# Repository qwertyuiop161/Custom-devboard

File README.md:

##Description

This is a custom devboard made with an ESP32-S3-WROOM-1 module using the preinstalled firmware. It uses a usb controller and a usb C port, with 5 main capacitors and 6 main resistors, along with 3 leds. the back (because im not good enough to have it all one sided YET (still learning (wow double paren (WOW QUAD PAREN)))) hsa an addressable LES with 2 more resistors and another capacitors.
I choose the ESP chip because of its power compared to arduino, WIFI and bluetooth capability, ease of wiring, and use of use. It has 40 pins, with 30 usable GPIO i think; also just wanted to mention that semicolon was a typo its just kinda funna that im so used to java and C that i accidentally end every sentence in typing with semicolon (even accidentally did iton this before correcting).

##Images:

###Schematic image:

Image of schematic:
<br>

###PCB images:

PCB full
<br>

PCB pads and zones
<br>

PCB tracks and vias
<br>

###3D Model images:

3D model front
<br>

3D model back
<br>

###BOM image:

BOM
<br>

###Bult Board:

Built Board! (sorry for low quality I have a bad camera):

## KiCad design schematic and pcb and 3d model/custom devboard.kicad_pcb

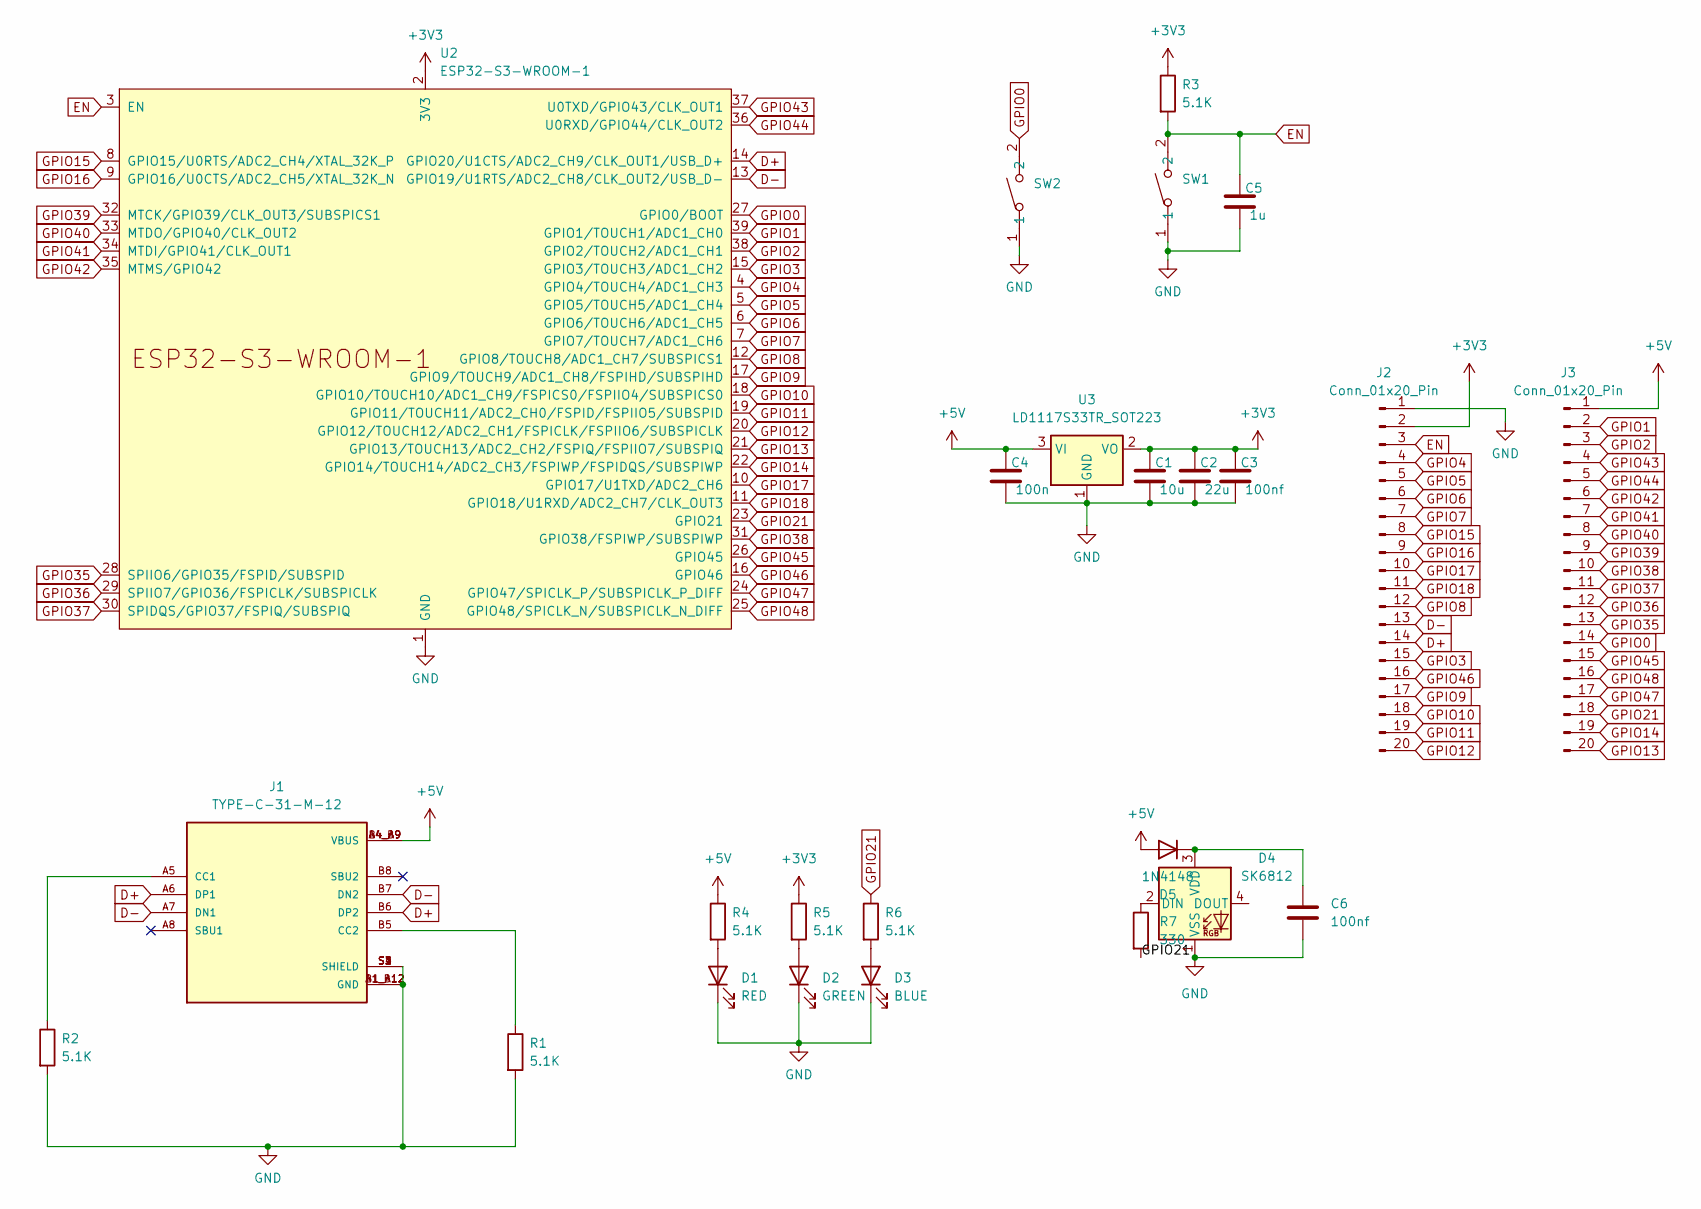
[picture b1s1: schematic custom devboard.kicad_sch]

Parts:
C1: 10u; C_0603_1608Metric
C2: 22u; C_0603_1608Metric
C3, C6: 100nf; C_0603_1608Metric
C4: 100n; C_0603_1608Metric
C5: 1u; C_0603_1608Metric
D1: RED; LED_0603_1608Metric
D2: GREEN; LED_0603_1608Metric
D3: BLUE; LED_0603_1608Metric
D4: SK6812; LED_SK6812_PLCC4_5.0x5.0mm_P3.2mm
D5: 1N4148; D_0603_1608Metric
J1: TYPE-C-31-M-12; HRO_TYPE-C-31-M-12; PARTREV 2020.12.08
J2, J3: Conn_01x20_Pin; PinHeader_1x20_P2.54mm_Vertical
R1, R2, R3, R4, R5, R6: 5.1K; R_0603_1608Metric
R7: 330; R_0603_1608Metric
SW1, SW2: TS-1088-AR02016; SW-SMD_L3.9-W3.0-P4.45; LCSC Part C720477
U2: ESP32-S3-WROOM-1
U3: LD1117S33TR_SOT223; SOT-223-3_TabPin2

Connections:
+3V3: C1.1, C2.1, C3.1, J2.2, R3.1, R5.1, U2.2 (3V3), U3.2 (VO)
+5V: C4.1, D5.2 (A), J1.A4_B9 (VBUS), J1.B4_A9 (VBUS), J3.1, R4.1, U3.3 (VI)
D+: J1.A6 (DP1), J1.B6 (DP2), J2.14, U2.14 (GPIO20/U1CTS/ADC2_CH9/CLK_OUT1/USB_D+)
D-: J1.A7 (DN1), J1.B7 (DN2), J2.13, U2.13 (GPIO19/U1RTS/ADC2_CH8/CLK_OUT2/USB_D-)
EN: C5.1, J2.3, R3.2, SW1.2, U2.3 (EN)
GND: C1.2, C2.2, C3.2, C4.2, C5.2, C6.2, D1.1 (K), D2.1 (K), D3.1 (K), D4.1 (VSS), J1.A1_B12 (GND), J1.B1_A12 (GND), J1.S1 (SHIELD), J1.S2 (SHIELD), J1.S3 (SHIELD), J1.S4 (SHIELD), J2.1, R1.2, R2.2, SW1.1, SW2.1, U2.1 (GND), U2.40 (GND), U2.41 (GND), U3.1 (GND)
GPIO0: J3.14, SW2.2, U2.27 (GPIO0/BOOT)
GPIO1: J3.2, U2.39 (GPIO1/TOUCH1/ADC1_CH0)
GPIO2: J3.3, U2.38 (GPIO2/TOUCH2/ADC1_CH1)
GPIO3: J2.15, U2.15 (GPIO3/TOUCH3/ADC1_CH2)
GPIO4: J2.4, U2.4 (GPIO4/TOUCH4/ADC1_CH3)
GPIO5: J2.5, U2.5 (GPIO5/TOUCH5/ADC1_CH4)
GPIO6: J2.6, U2.6 (GPIO6/TOUCH6/ADC1_CH5)
GPIO7: J2.7, U2.7 (GPIO7/TOUCH7/ADC1_CH6)
GPIO8: J2.12, U2.12 (GPIO8/TOUCH8/ADC1_CH7/SUBSPICS1)
GPIO9: J2.17, U2.17 (GPIO9/TOUCH9/ADC1_CH8/FSPIHD/SUBSPIHD)
GPIO10: J2.18, U2.18 (GPIO10/TOUCH10/ADC1_CH9/FSPICS0/FSPIIO4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)
GPIO11: J2.19, U2.19 (GPIO11/TOUCH11/ADC2_CH0/FSPID/FSPIIO5/S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)
GPIO12: J2.20, U2.20 (GPIO12/TOUCH12/ADC2_CH1/FSPICLK/FSPIIO6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)
GPIO13: J3.20, U2.21 (GPIO13/TOUCH13/ADC2_CH2/FSPIQ/FSPIIO7/S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)
GPIO14: J3.19, U2.22 (GPIO14/TOUCH14/ADC2_CH3/FSPIWP/FSPIDQS/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)
GPIO15: J2.8, U2.8 (GPIO15/U0RTS/ADC2_CH4/XTAL_32K_P)
GPIO16: J2.9, U2.9 (GPIO16/U0CTS/ADC2_CH5/XTAL_32K_N)
GPIO17: J2.10, U2.10 (GPIO17/U1TXD/ADC2_CH6)
GPIO18: J2.11, U2.11 (GPIO18/U1RXD/ADC2_CH7/CLK_OUT3)
GPIO21: J3.18, R6.1, R7.2, U2.23 (GPIO21)
GPIO35: J3.13, U2.28 (SPIIO6/GPIO35/FSPID/SUBSPID)
GPIO36: J3.12, U2.29 (SPIIO7/GPIO36/FSPICLK/SUBSPICLK)
GPIO37: J3.11, U2.30 (SPIDQS/GPIO37/FSPIQ/SUBSPIQ)
GPIO38: J3.10, U2.31 (GPIO38/FSPIWP/SUBSPIWP)
GPIO39: J3.9, U2.32 (MTCK/GPIO39/CLK_OUT3/SUBSPICS1)
GPIO40: J3.8, U2.33 (MTDO/GPIO40/CLK_OUT2)
GPIO41: J3.7, U2.34 (MTDI/GPIO41/CLK_OUT1)
GPIO42: J3.6, U2.35 (MTMS/GPIO42)
GPIO43: J3.4, U2.37 (U0TXD/GPIO43/CLK_OUT1)
GPIO44: J3.5, U2.36 (U0RXD/GPIO44/CLK_OUT2)
GPIO45: J3.15, U2.26 (GPIO45)
GPIO46: J2.16, U2.16 (GPIO46)
GPIO47: J3.17, U2.24 (GPIO47/SPICLK_P/SUBSPICLK_P_DIFF)
GPIO48: J3.16, U2.25 (GPIO48/SPICLK_N/SUBSPICLK_N_DIFF)
unnamed: D1.2 (A), R4.2
unnamed: D2.2 (A), R5.2
unnamed: D3.2 (A), R6.2
unnamed: D4.2 (DIN), R7.1
unnamed: C6.1, D4.3 (VDD), D5.1 (K)
unnamed: J1.A5 (CC1), R2.1
unnamed: J1.B5 (CC2), R1.1

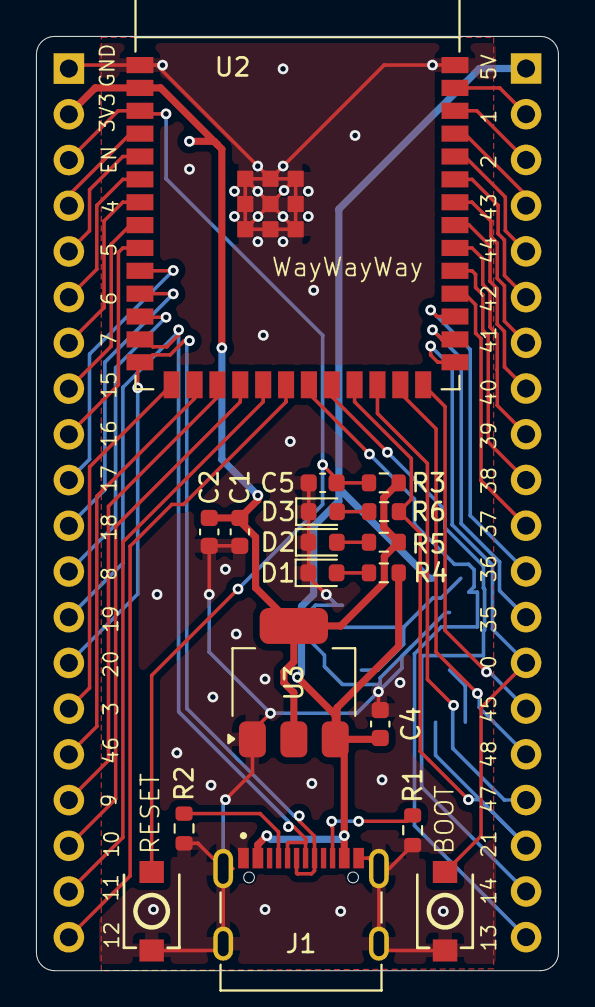
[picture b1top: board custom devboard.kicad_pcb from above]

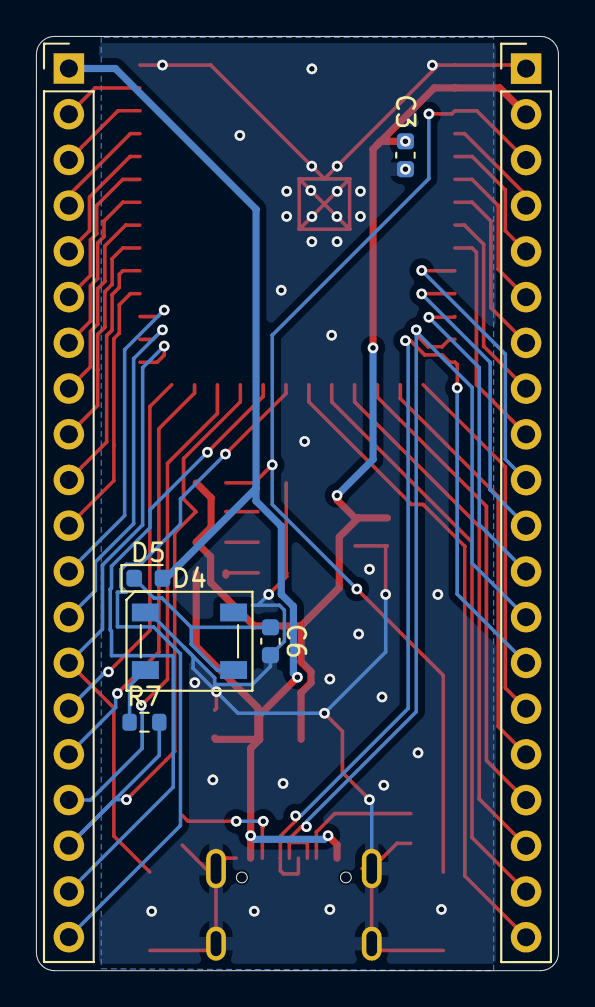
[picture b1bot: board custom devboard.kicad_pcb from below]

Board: 2 copper layers, 29.0 x 51.9 mm, 25 parts (7 on the bottom side), 47 nets.

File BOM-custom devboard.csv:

Comment,Designator,Footprint,LCSC,Quantity
100n,C4,C_0603_1608Metric,C14663,1
100nf,C3,C_0603_1608Metric,C14663,1
10u,C1,C_0603_1608Metric,C19702,1
1u,C5,C_0603_1608Metric,C14664,1
22u,C2,C_0603_1608Metric,C24438055,1
5.1K,"R1,R2,R3,R4,R5,R6",R_0603_1608Metric,C105580,6
BLUE,D3,LED_0603_1608Metric,C72041,1
Conn_01x20_Pin,"J2,J3",PinHeader_1x20_P2.54mm_Vertical,C7501591,2
ESP32-S3-WROOM-1,U2,ESP32-S3-WROOM-1,C2913202,1
GREEN,D2,LED_0603_1608Metric,C72043,1
LD1117S33TR_SOT223,U3,SOT-223-3_TabPin2,C86781,1
RED,D1,LED_0603_1608Metric,C2286,1
TS-1088-AR02016,"SW1,SW2",SW-SMD_L3.9-W3.0-P4.45,C720477,2
TYPE-C-31-M-12,J1,HRO_TYPE-C-31-M-12,C165948,1

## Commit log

2026-05-17 Enhance README with project details
    Updated project description to provide more context about the PCB design and its purpose.
2026-05-23 Enhance README with PCB design details and images
    Added additional information about the PCB design, including images of the schematic, PCB layouts, and a 3D model.
2026-05-23 Fix formatting and add new images in README
    Updated formatting for schematic, PCB, and model sections.
2026-05-23 Update README with images and formatting corrections
2026-05-23 Add README content for custom devboard
    Added detailed description of the custom devboard, including specifications, images, and links to schematics.
2026-06-01 Revise README with images and formatting changes
    Updated README to include images and correct links.
2026-06-01 Revise README formatting and add images
    Updated section headers and added images for schematic, PCB, 3D model, and BOM.
